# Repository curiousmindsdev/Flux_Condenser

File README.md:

# Flux Condenser Rev.3

### What is it?

A tiny (35mm x 25mm) PCB badge featuring 24 LEDs that animate to create the “fluxxing” effect. It’s 100% decorative, it doesn’t actually let you travel through time when worn around the neck.

It is controlled by a Microchip ATtiny816 microcontroller. Thankfully this board has a much lower power requirement than the silkscreen indicates on the back, and skips along, sipping power from the single CR2032/LIR2032 coin cell battery (instead of plutonium or a lightning strike), slipped into the rear mounted coin cell holder.

https://user-images.githubusercontent.com/56890227/131141057-b0eb6197-e710-4d84-89a1-9ab057af56d6.mov

https://user-images.githubusercontent.com/56890227/131141300-c1670cdc-f619-4a5a-8890-5401563677f6.mov

### What is changed from Rev.2 to Rev.3?

Thanks to Microchip’s latest ATtiny816 microcontroller now I can dim the LEDs with 8 individual PWM pins. Users can now change the animation type, animation speed, and LED brightness. There are 2 animation types (multi beam and single beam), 2 animation speeds (slow and fast), 4 LED brightness levels (100%, 75%, 50% and 25%).  Power consumption is drastically lowered. At full brightness it draws 2.3mA and at 25% brightness it draws 1.1mA of current from the battery. Also front of the Flux Condenser is now much cleaner. Most of the via drill holes are gone.

### How long will the battery last?

CR2032 (Non-Rechargeable) with average of 210mAh battery capacity.
-	100% LED Brightness :   91 Hours
-	25% LED Brightness	 :   190 Hours

LIR2032 (Rechargeable) with average of 40mAh battery capacity.
-	100% LED Brightness :   17 Hours
-	25% LED Brightness	 :   36 Hours

### Configuration 

To set your desired animation, speed and LED brightness, you have to start flux condenser with configuration interface. In order to do that, you have to turn off your flux condenser. While holding the “Start” button on the back turn the flux condenser on. Now you should see configuration interface. Some of the LEDs should be on and some off according to your configuration. LEDs on each row of all columns, starting from outer to inner are paralleled.  

Each LED number from photo shown above represents different setting.

- LED1 : Single Beam Animation
- LED2 : Multi Beam Animation
- LED3 : Slow Animation Speed
- LED4 : Fast Animation Speed
- LED5 : 100% LED Brightness
- LED6 : 75% LED Brightness
- LED7 : 50% LED Brightness
- LED8 : 25% LED Brightness

To choose your preference just hold the start button. All the LEDs should turn off and after a second starting from LED1 each individual LED gets lit. Hold the start until the LED that represents your preferred setting is lit, then release the button. Now your new configuration is set. To see it in more detail check out the video below.

https://www.youtube.com/watch?v=2X2gqoI-mSA

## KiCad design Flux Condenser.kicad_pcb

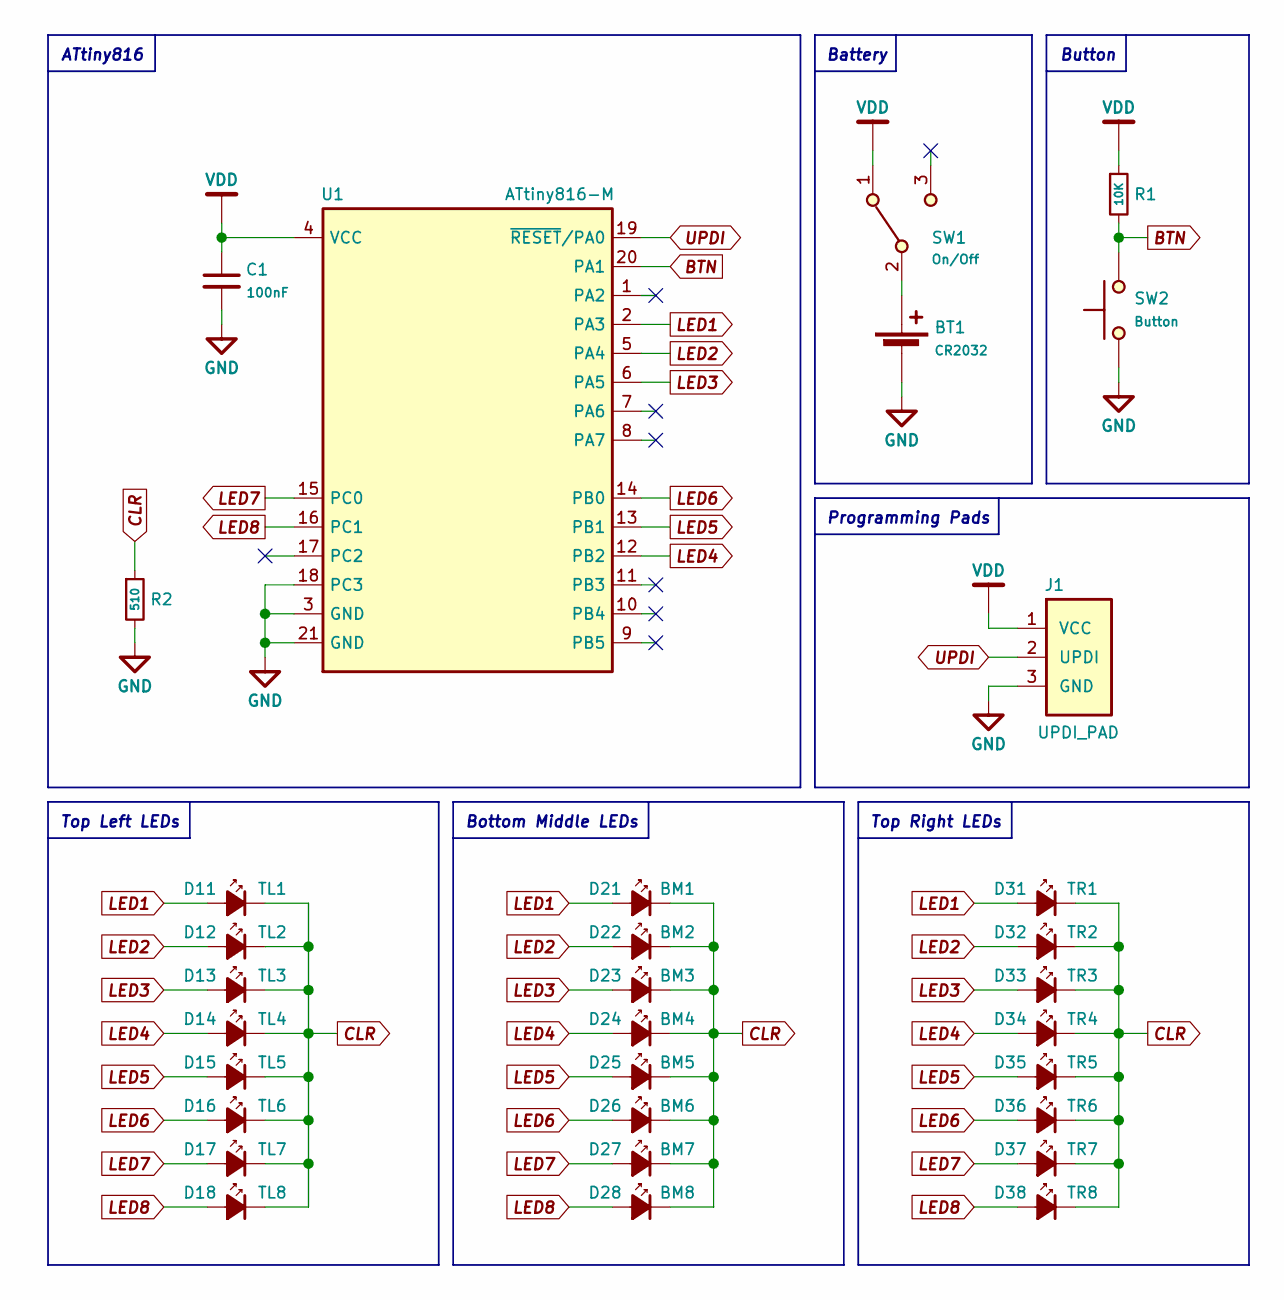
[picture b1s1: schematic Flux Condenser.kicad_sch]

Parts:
BT1: CR2032; CR2032_Metal_Battery_Holder
C1: 100nF; C_0402_1005Metric
D11: TL1; LED_0402_1005Metric
D12: TL2; LED_0402_1005Metric
D13: TL3; LED_0402_1005Metric
D14: TL4; LED_0402_1005Metric
D15: TL5; LED_0402_1005Metric
D16: TL6; LED_0402_1005Metric
D17: TL7; LED_0402_1005Metric
D18: TL8; LED_0402_1005Metric
D21: BM1; LED_0402_1005Metric
D22: BM2; LED_0402_1005Metric
D23: BM3; LED_0402_1005Metric
D24: BM4; LED_0402_1005Metric
D25: BM5; LED_0402_1005Metric
D26: BM6; LED_0402_1005Metric
D27: BM7; LED_0402_1005Metric
D28: BM8; LED_0402_1005Metric
D31: TR1; LED_0402_1005Metric
D32: TR2; LED_0402_1005Metric
D33: TR3; LED_0402_1005Metric
D34: TR4; LED_0402_1005Metric
D35: TR5; LED_0402_1005Metric
D36: TR6; LED_0402_1005Metric
D37: TR7; LED_0402_1005Metric
D38: TR8; LED_0402_1005Metric
J1: UPDI_PAD; PogoPad_1x03_P1.27mm
R1: 10K; R_0402_1005Metric
R2: 510; R_0402_1005Metric
SW1: On/Off; SSAJ120100
SW2: Button; SW_Push_KH
U1: ATtiny816-M; VQFN-20-1EP_3x3mm_P0.4mm_EP1.7x1.7mm

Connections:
BTN: R1.2, SW2.2, U1.20 (PA1)
CLR: D11.1 (K), D12.1 (K), D13.1 (K), D14.1 (K), D15.1 (K), D16.1 (K), D17.1 (K), D18.1 (K), D21.1 (K), D22.1 (K), D23.1 (K), D24.1 (K), D25.1 (K), D26.1 (K), D27.1 (K), D28.1 (K), D31.1 (K), D32.1 (K), D33.1 (K), D34.1 (K), D35.1 (K), D36.1 (K), D37.1 (K), D38.1 (K), R2.1
GND: BT1.2 (-), C1.2, J1.3 (GND), R2.2, SW2.1, U1.3 (GND), U1.18 (PC3), U1.21 (GND)
LED1: D11.2 (A), D21.2 (A), D31.2 (A), U1.2 (PA3)
LED2: D12.2 (A), D22.2 (A), D32.2 (A), U1.5 (PA4)
LED3: D13.2 (A), D23.2 (A), D33.2 (A), U1.6 (PA5)
LED4: D14.2 (A), D24.2 (A), D34.2 (A), U1.12 (PB2)
LED5: D15.2 (A), D25.2 (A), D35.2 (A), U1.13 (PB1)
LED6: D16.2 (A), D26.2 (A), D36.2 (A), U1.14 (PB0)
LED7: D17.2 (A), D27.2 (A), D37.2 (A), U1.15 (PC0)
LED8: D18.2 (A), D28.2 (A), D38.2 (A), U1.16 (PC1)
unnamed: BT1.1 (+), SW1.2 (B)
UPDI: J1.2 (UPDI), U1.19 (~RESET~/PA0)
VDD: C1.1, J1.1 (VCC), R1.1, SW1.1 (A), U1.4 (VCC)

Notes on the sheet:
ATtiny816
Top Left LEDs
Bottom Middle LEDs
Battery
Programming Pads
Top Right LEDs
Button

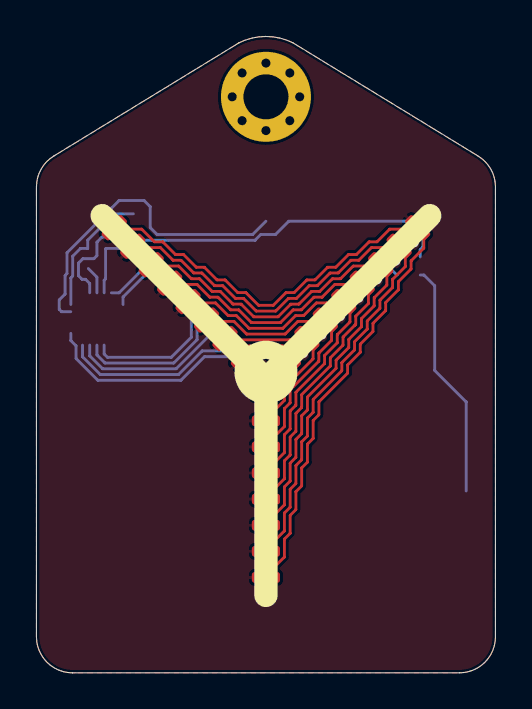
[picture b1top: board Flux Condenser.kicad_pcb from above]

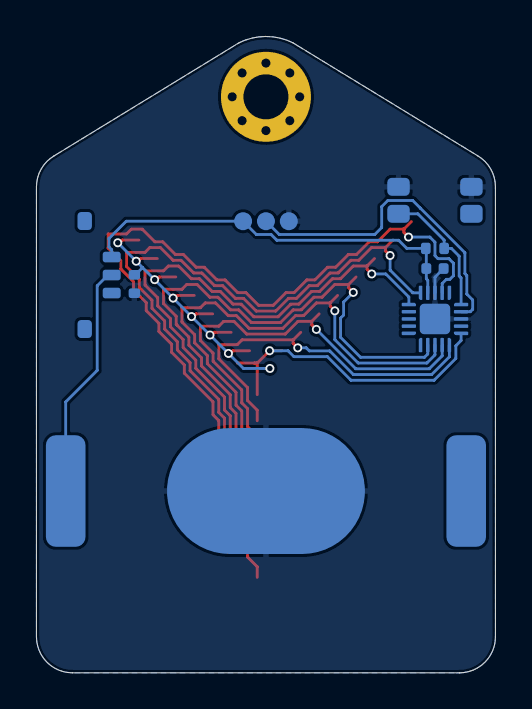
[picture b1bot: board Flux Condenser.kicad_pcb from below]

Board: 2 copper layers, 25.5 x 35.4 mm, 37 parts (12 on the bottom side), 14 nets.

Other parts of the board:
svg2mod, svg2mod#2, svg2mod#3, svg2mod#4, svg2mod#5: G***; svg2mod

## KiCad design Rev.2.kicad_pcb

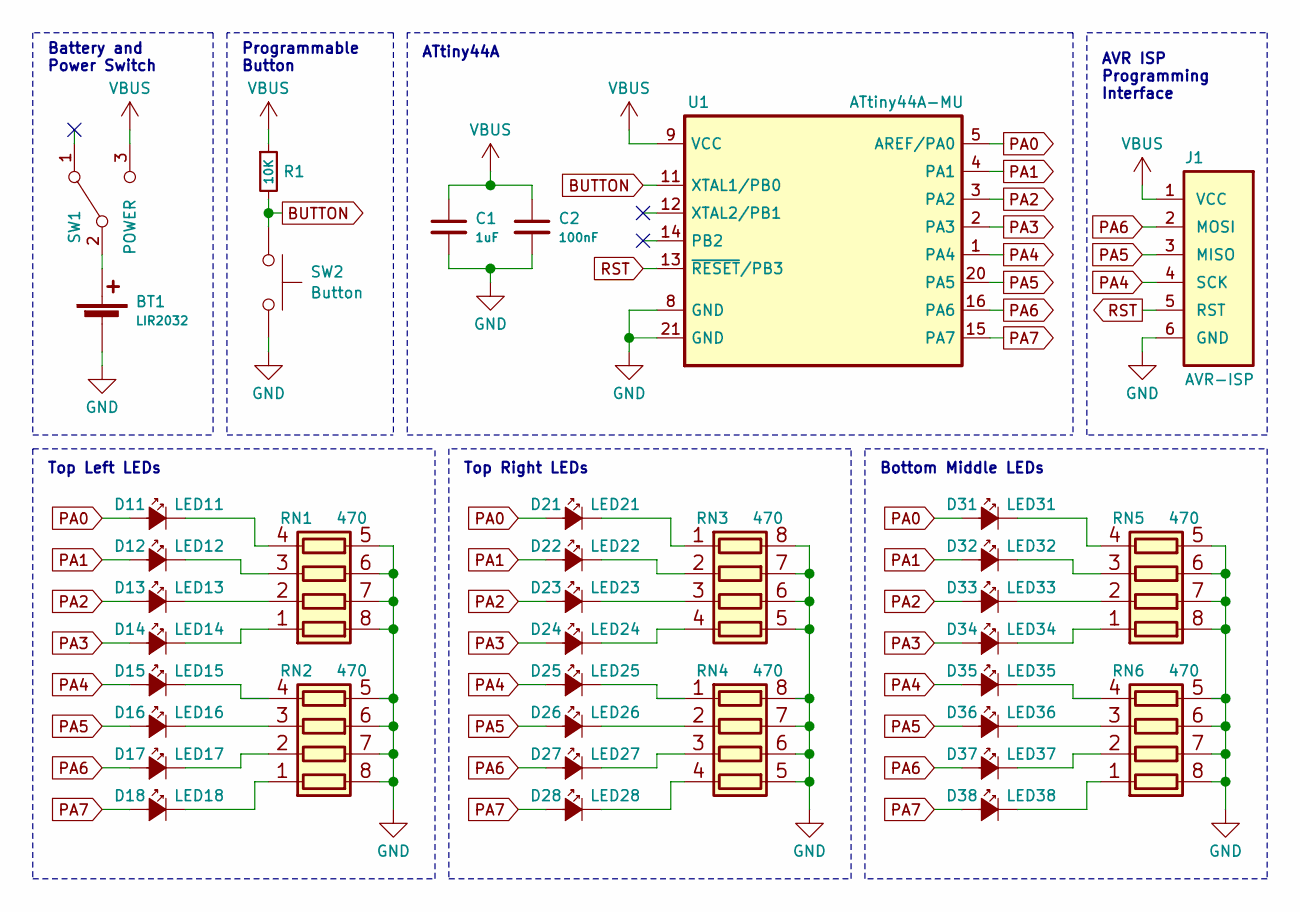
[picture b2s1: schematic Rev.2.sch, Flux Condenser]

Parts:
BT1: LIR2032; CR2032_Metal_Battery_Holder
C1: 1uF; C_0402_1005Metric
C2: 100nF; C_0402_1005Metric
D11: LED11; LED_0402_1005Metric
D12: LED12; LED_0402_1005Metric
D13: LED13; LED_0402_1005Metric
D14: LED14; LED_0402_1005Metric
D15: LED15; LED_0402_1005Metric
D16: LED16; LED_0402_1005Metric
D17: LED17; LED_0402_1005Metric
D18: LED18; LED_0402_1005Metric
D21: LED21; LED_0402_1005Metric
D22: LED22; LED_0402_1005Metric
D23: LED23; LED_0402_1005Metric
D24: LED24; LED_0402_1005Metric
D25: LED25; LED_0402_1005Metric
D26: LED26; LED_0402_1005Metric
D27: LED27; LED_0402_1005Metric
D28: LED28; LED_0402_1005Metric
D31: LED31; LED_0402_1005Metric
D32: LED32; LED_0402_1005Metric
D33: LED33; LED_0402_1005Metric
D34: LED34; LED_0402_1005Metric
D35: LED35; LED_0402_1005Metric
D36: LED36; LED_0402_1005Metric
D37: LED37; LED_0402_1005Metric
D38: LED38; LED_0402_1005Metric
J1: AVR-ISP; PinHeader_1x06_P1.27mm_Vertical
R1: 10K; R_0402_1005Metric
RN1, RN2, RN3, RN4, RN5, RN6: 470; R_Array_Convex_4x0402
SW1: POWER; SSAJ120100
SW2: Button; SW_Push_KH
U1: ATtiny44A-MU; QFN-20-1EP_4x4mm_P0.5mm_EP2.6x2.6mm

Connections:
BUTTON: R1.2, SW2.1, U1.11 (XTAL1/PB0)
GND: BT1.2 (-), C1.2, C2.2, J1.6 (GND), RN1.5 (R4.2), RN1.6 (R3.2), RN1.7 (R2.2), RN1.8 (R1.2), RN2.5 (R4.2), RN2.6 (R3.2), RN2.7 (R2.2), RN2.8 (R1.2), RN3.5 (R4.2), RN3.6 (R3.2), RN3.7 (R2.2), RN3.8 (R1.2), RN4.5 (R4.2), RN4.6 (R3.2), RN4.7 (R2.2), RN4.8 (R1.2), RN5.5 (R4.2), RN5.6 (R3.2), RN5.7 (R2.2), RN5.8 (R1.2), RN6.5 (R4.2), RN6.6 (R3.2), RN6.7 (R2.2), RN6.8 (R1.2), SW2.2, U1.8 (GND), U1.21 (GND)
unnamed: BT1.1 (+), SW1.2 (B)
unnamed: D11.1 (K), RN1.4 (R4.1)
unnamed: D12.1 (K), RN1.3 (R3.1)
unnamed: D13.1 (K), RN1.2 (R2.1)
unnamed: D14.1 (K), RN1.1 (R1.1)
unnamed: D15.1 (K), RN2.4 (R4.1)
unnamed: D16.1 (K), RN2.3 (R3.1)
unnamed: D17.1 (K), RN2.2 (R2.1)
unnamed: D18.1 (K), RN2.1 (R1.1)
unnamed: D21.1 (K), RN3.1 (R1.1)
unnamed: D22.1 (K), RN3.2 (R2.1)
unnamed: D23.1 (K), RN3.3 (R3.1)
unnamed: D24.1 (K), RN3.4 (R4.1)
unnamed: D25.1 (K), RN4.1 (R1.1)
unnamed: D26.1 (K), RN4.2 (R2.1)
unnamed: D27.1 (K), RN4.3 (R3.1)
unnamed: D28.1 (K), RN4.4 (R4.1)
unnamed: D31.1 (K), RN5.4 (R4.1)
unnamed: D32.1 (K), RN5.3 (R3.1)
unnamed: D33.1 (K), RN5.2 (R2.1)
unnamed: D34.1 (K), RN5.1 (R1.1)
unnamed: D35.1 (K), RN6.4 (R4.1)
unnamed: D36.1 (K), RN6.3 (R3.1)
unnamed: D37.1 (K), RN6.2 (R2.1)
unnamed: D38.1 (K), RN6.1 (R1.1)
PA0: D11.2 (A), D21.2 (A), D31.2 (A), U1.5 (AREF/PA0)
PA1: D12.2 (A), D22.2 (A), D32.2 (A), U1.4 (PA1)
PA2: D13.2 (A), D23.2 (A), D33.2 (A), U1.3 (PA2)
PA3: D14.2 (A), D24.2 (A), D34.2 (A), U1.2 (PA3)
PA4: D15.2 (A), D25.2 (A), D35.2 (A), J1.4 (SCK), U1.1 (PA4)
PA5: D16.2 (A), D26.2 (A), D36.2 (A), J1.3 (MISO), U1.20 (PA5)
PA6: D17.2 (A), D27.2 (A), D37.2 (A), J1.2 (MOSI), U1.16 (PA6)
PA7: D18.2 (A), D28.2 (A), D38.2 (A), U1.15 (PA7)
RST: J1.5 (RST), U1.13 (~RESET~/PB3)
VBUS: C1.1, C2.1, J1.1 (VCC), R1.1, SW1.3 (C), U1.9 (VCC)

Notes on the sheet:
Top Left LEDs
Top Right LEDs
Bottom Middle LEDs
ATtiny44A
AVR ISP Programming Interface
Programmable Button
Battery and Power Switch

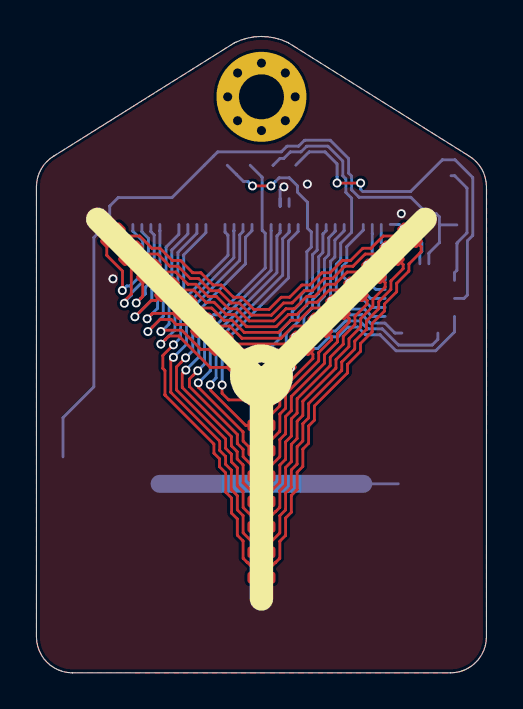
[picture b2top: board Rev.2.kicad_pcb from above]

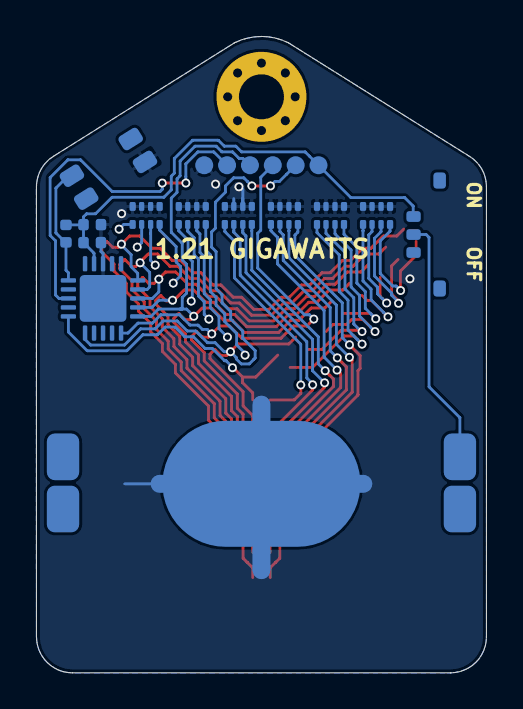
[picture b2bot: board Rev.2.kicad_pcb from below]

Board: 2 copper layers, 25.0 x 35.4 mm, 38 parts (14 on the bottom side), 37 nets.

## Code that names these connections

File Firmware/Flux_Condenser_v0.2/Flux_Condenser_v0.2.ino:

int led1 = PA0;
int led2 = PA1;
int led3 = PA2;
int led4 = PA3;
int led5 = PA4;
int led6 = PA5;
int led7 = PA6;
int led8 = PA7;

void setup() {                
  pinMode(led1, OUTPUT); 
  pinMode(led2, OUTPUT);
  pinMode(led3, OUTPUT);
  pinMode(led4, OUTPUT);
  pinMode(led5, OUTPUT);
  pinMode(led6, OUTPUT);
  pinMode(led7, OUTPUT);
  pinMode(led8, OUTPUT);    
}

void loop() {
  digitalWrite(led1, HIGH);
  digitalWrite(led6, HIGH);
  digitalWrite(led7, HIGH);
  delay(50); 
  digitalWrite(led1, HIGH);
  digitalWrite(led2, HIGH);
  digitalWrite(led7, HIGH);
  digitalWrite(led8, HIGH);
  digitalWrite(led6, LOW);
  delay(50);
  digitalWrite(led2, HIGH);
  digitalWrite(led3, HIGH);
  digitalWrite(led8, HIGH);
  digitalWrite(led1, LOW);
  digitalWrite(led7, LOW);
  delay(50);
  digitalWrite(led3, HIGH);
  digitalWrite(led4, HIGH);
  digitalWrite(led2, LOW);
  digitalWrite(led8, LOW);
  delay(50);
  digitalWrite(led4, HIGH);
  digitalWrite(led5, HIGH);
  digitalWrite(led3, LOW);
  delay(50);
  digitalWrite(led5, HIGH);
  digitalWrite(led6, HIGH);
  digitalWrite(led4, LOW);
  delay(50);
  digitalWrite(led5, LOW);
}

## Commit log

2020-11-08 Rename Flux_Condenser_v0.3.ino.ino to Flux_Condenser_v0.3.ino
2020-12-12 Rename Firmware/Flux_Condenser_v0.4.ino/Flux_Condenser_v0.4.ino to Firmware/Flux_Condenser_v0.4/Flux_Condenser_v0.4.ino

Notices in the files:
Rev.2.kicad_pcb:
GNU General Public License v3.0
